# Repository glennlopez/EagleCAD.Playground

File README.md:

<!-- https://github.com/adam-p/markdown-here/wiki/Markdown-Cheatsheet -->

EagleCAD Playground
=================
This is where I host all my EagleCAD files that are non-project related. Most are trials, some are personal mini projects, others eventually make it to become its own larger project which are then moved into its own repository never to be seen here ever again.

>EAGLE (for: Easily Applicable Graphical Layout Editor, German: Einfach anzuwendender grafischer Layout-Editor) by CadSoft Computer is a flexible, expandable and scriptable EDA application with schematic capture editor, PCB layout editor, auto-router and CAM and BOM tools developed by CadSoft Computer GmbH, Germany, since 1988.

The CNC files for milling the PCB's are stored in [my Dropbox](https://www.dropbox.com/sh/d38r4gpvw2gcx58/AAAy57JtkxvIMt3Gzy3qRX3Ka) account to simplify my workflow (syncing between my CNC Milling work-station and Design work-station | <i>you may need permission to access them)</i>.

### Folder Structure

| Folder Name        | Description           |
| ------------- |:--------------------:| 
| DESIGN RULES     | For designing PCBs in Eagle. This is a list of rules that I have forged over the years | 
| PROJECTS     | where you will find all EagleCAD projects| 
| SCRIPTS     | Scripts I created/and use for automating tasks | 
| USER LIBRARY     | Collection of libraries I created/and use | 
| CAM    | Collection of CAM files for converting brd files to gerber | 
| PCB-GCODE | used to convert brd files to gcode | 

### Learning/Referance material
* https://www.sparkfun.com/tutorials/108
* https://www.sparkfun.com/tutorials/115
* http://www.jeremyblum.com/?s=Eagle+cad
* http://www.build-electronic-circuits.com/eagle-scripts/
* http://www.cadsoftusa.com/training/tutorials/?language=en

### Recomended Downloads
* http://www.cadsoftusa.com/download-eagle/?language=en

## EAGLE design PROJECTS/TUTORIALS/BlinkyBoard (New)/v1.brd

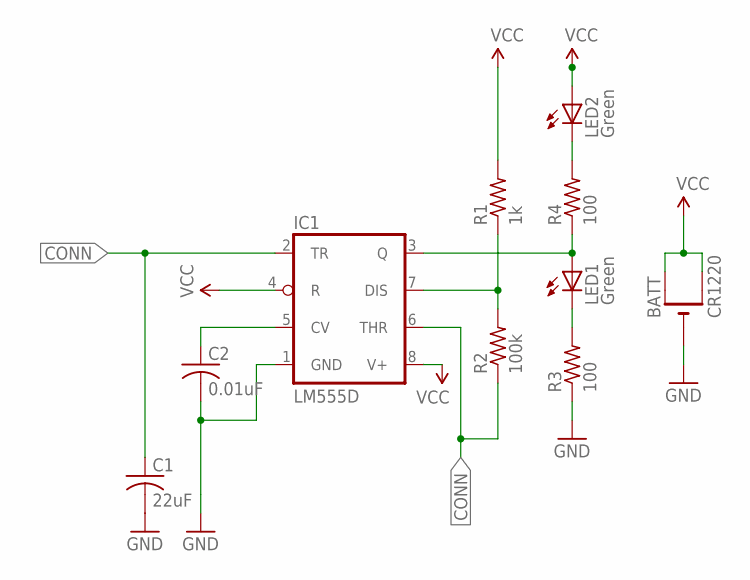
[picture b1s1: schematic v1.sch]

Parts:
BATT: CR1220; CR1220-SMD
C1: 22uF; C0805; MPN C0805C224K4RACTU
C2: 0.01uF; C0805; MPN 08051C103KAT2A
IC1: LM555D; SO08; MPN LM555CM
LED1, LED2: Green; CHIPLED_0805; MPN 5988160107F.
R1: 1k; R0805; MPN CRCW08051K00FKTA
R2: 100k; R0805; MPN MCHV05WAJ0104T5E
R3, R4: 100; R0805; MPN CRCW08051K00FKTA

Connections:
CONN: C1.1, IC1.2 (TR), IC1.6 (THR), R2.1
GND: BATT.-, C1.2, R3.1
unnamed: LED2.C, R4.2
unnamed: IC1.3 (Q), LED1.A, R4.1
unnamed: LED1.C, R3.2
unnamed: IC1.7 (DIS), R1.1, R2.2
unnamed: C2.1, IC1.5 (CV)
unnamed: C2.2, IC1.1 (GND)
VCC: BATT.+$1 (+), BATT.+$2 (+1), IC1.4 (R), IC1.8 (V+), LED2.A, R1.2

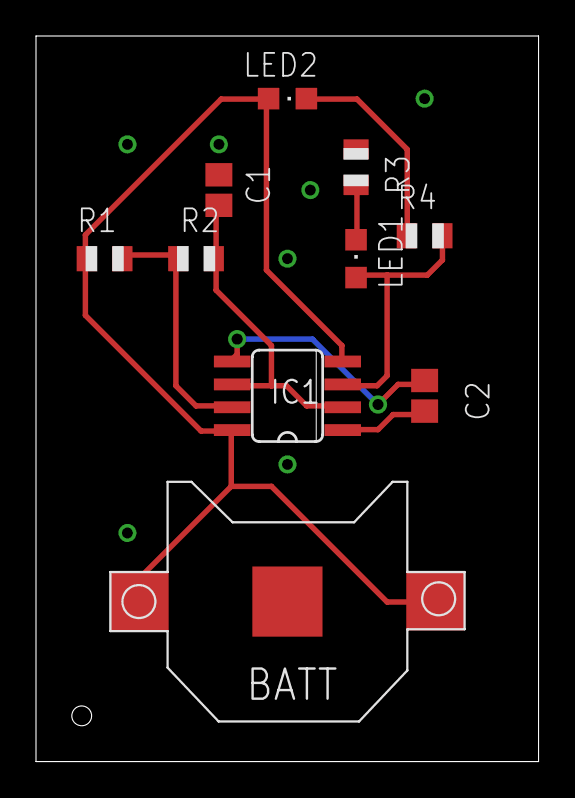
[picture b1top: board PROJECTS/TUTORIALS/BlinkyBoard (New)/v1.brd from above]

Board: 2 copper layers, 27.9 x 40.3 mm, 10 parts (0 on the bottom side), 9 nets.

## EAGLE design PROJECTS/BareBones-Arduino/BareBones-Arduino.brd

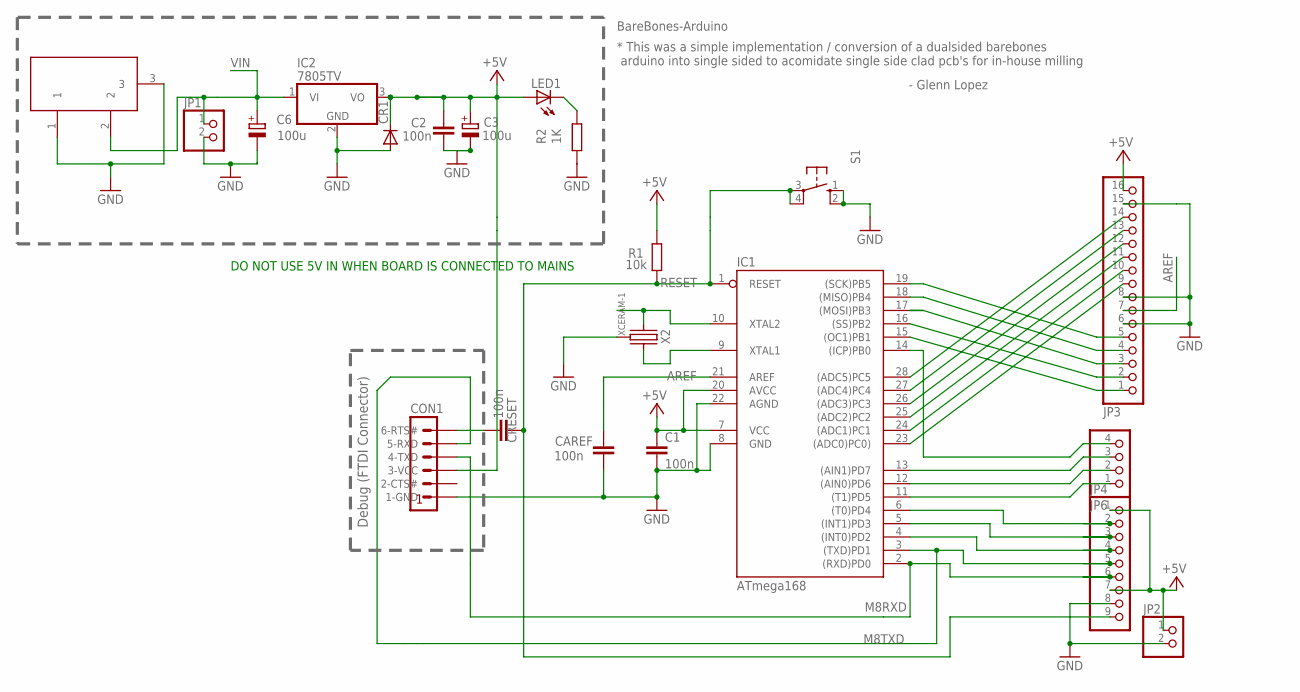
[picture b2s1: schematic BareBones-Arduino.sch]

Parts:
C1: 100n; C025-025X050
C2: 100n; C1206K
C3, C6: 100u; E2,5-7
CAREF: 100n; C1206K
CON1: FTDI-TTL232R; MA06-1
CR1: DIODE-1ARECT-2V; DO41-2V
CRESET: 100n; C025-025X050
IC1: ATmega168; DIL28-3
IC2: 7805TV; TO220V
JP1, JP2: PINHD-1X2; 1X02
JP3: PINHD-1X16-BARE; 1X16-BARE
JP4: PINHD-1X9-BARE; 1X09-BARE
JP6: PINHD-1X4-BARE; 1X04-BARE
LED1: LED3MM
R1: 10k; 0204/5
R2: 1K; 0204/5
S1: 10-XX; B3F-10XX
X2: XCERAM-1; XTAL-3
X3: DC-In; 4UCON-POWER-JACK

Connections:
+5V: C1.1, C2.2, C3.+, CON1.3 (3-VCC), CR1.C, IC1.7 (VCC), IC1.20 (AVCC), IC2.3 (VO), JP2.1, JP3.16, JP4.1, JP4.7, LED1.A, R1.2
AREF: CAREF.2, IC1.21 (AREF), JP3.7
GND: C1.2, C2.1, C3.-, C6.-, CAREF.1, CON1.1 (1-GND), CR1.A, IC1.8 (GND), IC1.22 (AGND), IC2.2 (GND), JP1.2, JP2.2, JP3.6, JP3.8, JP3.15, JP4.8, R2.2, S1.1 (S), S1.2 (S1), X2.P$2 (GND), X3.1, X3.3
M8RXD: CON1.4 (4-TXD), IC1.2 ((RXD)PD0), JP4.6
M8TXD: CON1.5 (5-RXD), IC1.3 ((TXD)PD1), JP4.5
unnamed: IC1.18 ((MISO)PB4), JP3.4
unnamed: LED1.K (C), R2.1
unnamed: IC1.24 ((ADC1)PC1), JP3.10
unnamed: IC1.17 ((MOSI)PB3), JP3.3
unnamed: IC1.11 ((T1)PD5), JP6.1
unnamed: IC1.9 (XTAL1), X2.P$3
unnamed: IC1.10 (XTAL2), X2.P$1
unnamed: CON1.6 (6-RTS#), CRESET.1
unnamed: IC1.4 ((INT0)PD2), JP4.4
unnamed: IC1.5 ((INT1)PD3), JP4.3
unnamed: IC1.6 ((T0)PD4), JP4.2
unnamed: IC1.12 ((AIN0)PD6), JP6.2
unnamed: IC1.13 ((AIN1)PD7), JP6.3
unnamed: IC1.14 ((ICP)PB0), JP6.4
unnamed: IC1.15 ((OC1)PB1), JP3.1
unnamed: IC1.16 ((SS)PB2), JP3.2
unnamed: IC1.23 ((ADC0)PC0)), JP3.9
unnamed: IC1.25 ((ADC2)PC2), JP3.11
unnamed: IC1.26 ((ADC3)PC3), JP3.12
unnamed: IC1.27 ((ADC4)PC4), JP3.13
unnamed: IC1.28 ((ADC5)PC5), JP3.14
RESET: CRESET.2, IC1.1 (RESET), JP4.9, R1.1, S1.3, S1.4 (P1)
SCK: IC1.19 ((SCK)PB5), JP3.5
VIN: C6.+, IC2.1 (VI), JP1.1, X3.2

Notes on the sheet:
Debug (FTDI Connector)
BareBones-Arduino
- Glenn Lopez
* This was a simple implementation / conversion of a dualsided barebones arduino into single sided to acomidate single side clad pcb's for in-house milling
DO NOT USE 5V IN WHEN BOARD IS CONNECTED TO MAINS

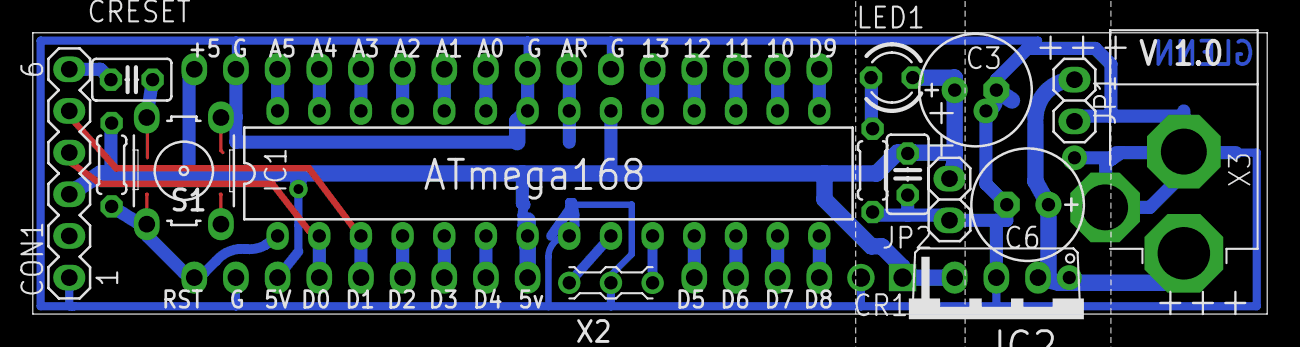
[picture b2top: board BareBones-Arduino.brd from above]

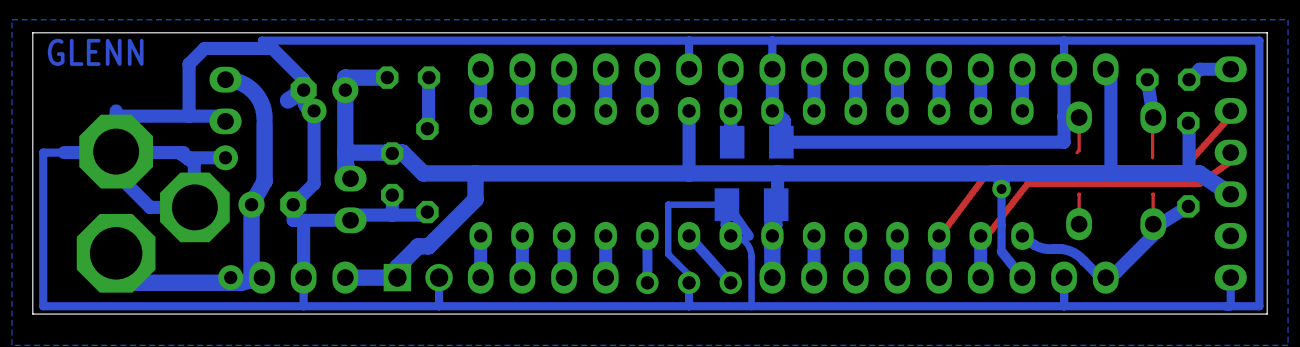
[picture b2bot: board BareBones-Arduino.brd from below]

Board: 2 copper layers, 75.2 x 17.1 mm, 21 parts (2 on the bottom side), 29 nets.

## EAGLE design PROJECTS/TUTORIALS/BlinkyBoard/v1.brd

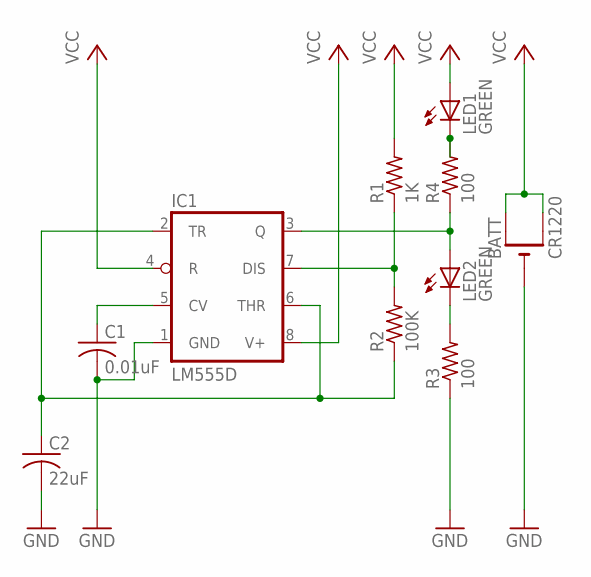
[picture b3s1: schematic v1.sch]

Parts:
BATT: CR1220; CR1220-SMD
C1: 0.01uF; C0805; MPN 08051C103KAT2A
C2: 22uF; C0805; MPN C2012X5R1A226K125AB
IC1: LM555D; SO08; MPN LM555CM
LED1, LED2: GREEN; CHIP-LED0805; MPN 150080VS75000
R1: 1K; R0805; MPN ERA-6APB102P
R2: 100K; R0805; MPN CRCW0805100KFKTA
R3, R4: 100; R0805; MPN CRCW0805100RJNEA

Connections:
GND: BATT.-, C1.2, C2.2, IC1.1 (GND), R3.1
unnamed: LED1.C, R4.2
unnamed: IC1.3 (Q), LED2.A, R4.1
unnamed: LED2.C, R3.2
unnamed: IC1.7 (DIS), R1.1, R2.2
unnamed: C2.1, IC1.2 (TR), IC1.6 (THR), R2.1
unnamed: C1.1, IC1.5 (CV)
VCC: BATT.+$1 (+), BATT.+$2 (+1), IC1.4 (R), IC1.8 (V+), LED1.A, R1.2

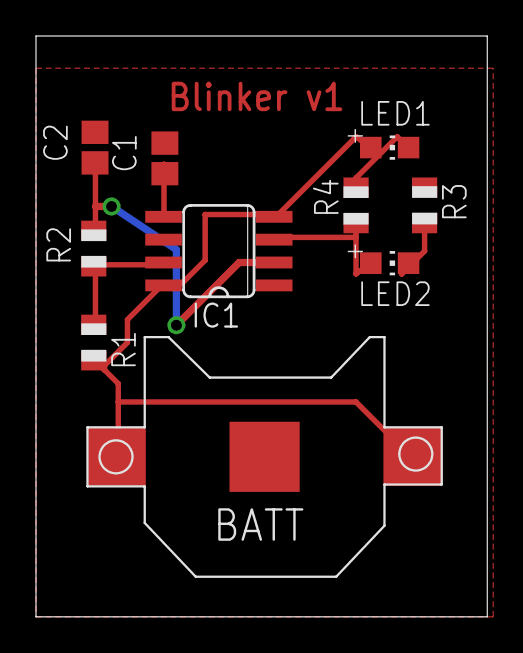
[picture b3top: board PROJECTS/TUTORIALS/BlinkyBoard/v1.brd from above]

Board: 2 copper layers, 25.1 x 32.3 mm, 10 parts (0 on the bottom side), 8 nets.

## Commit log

2014-06-03 folders
2014-06-03 folder structure created
2014-06-03 initial readme structure
2014-06-04 added sparkfun library
2014-07-10 updated read me
    changed gerber to EagleCAD
2014-07-10 fixed readme
2014-07-11 update
    finished tutorial 02
2014-07-11 update
    added pcb-gcode converter
2014-10-31 update file names
2015-05-18 repo cleanup
2015-05-20 updated
    added some stuff
2015-05-21 added plc board
    lpc probe added

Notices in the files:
parts and their libraries:
SparkFun-Aesthetics: Licensing: Creative Commons ShareAlike 4.0 International - https://creativecommons.org/licenses/by-sa/4.0
